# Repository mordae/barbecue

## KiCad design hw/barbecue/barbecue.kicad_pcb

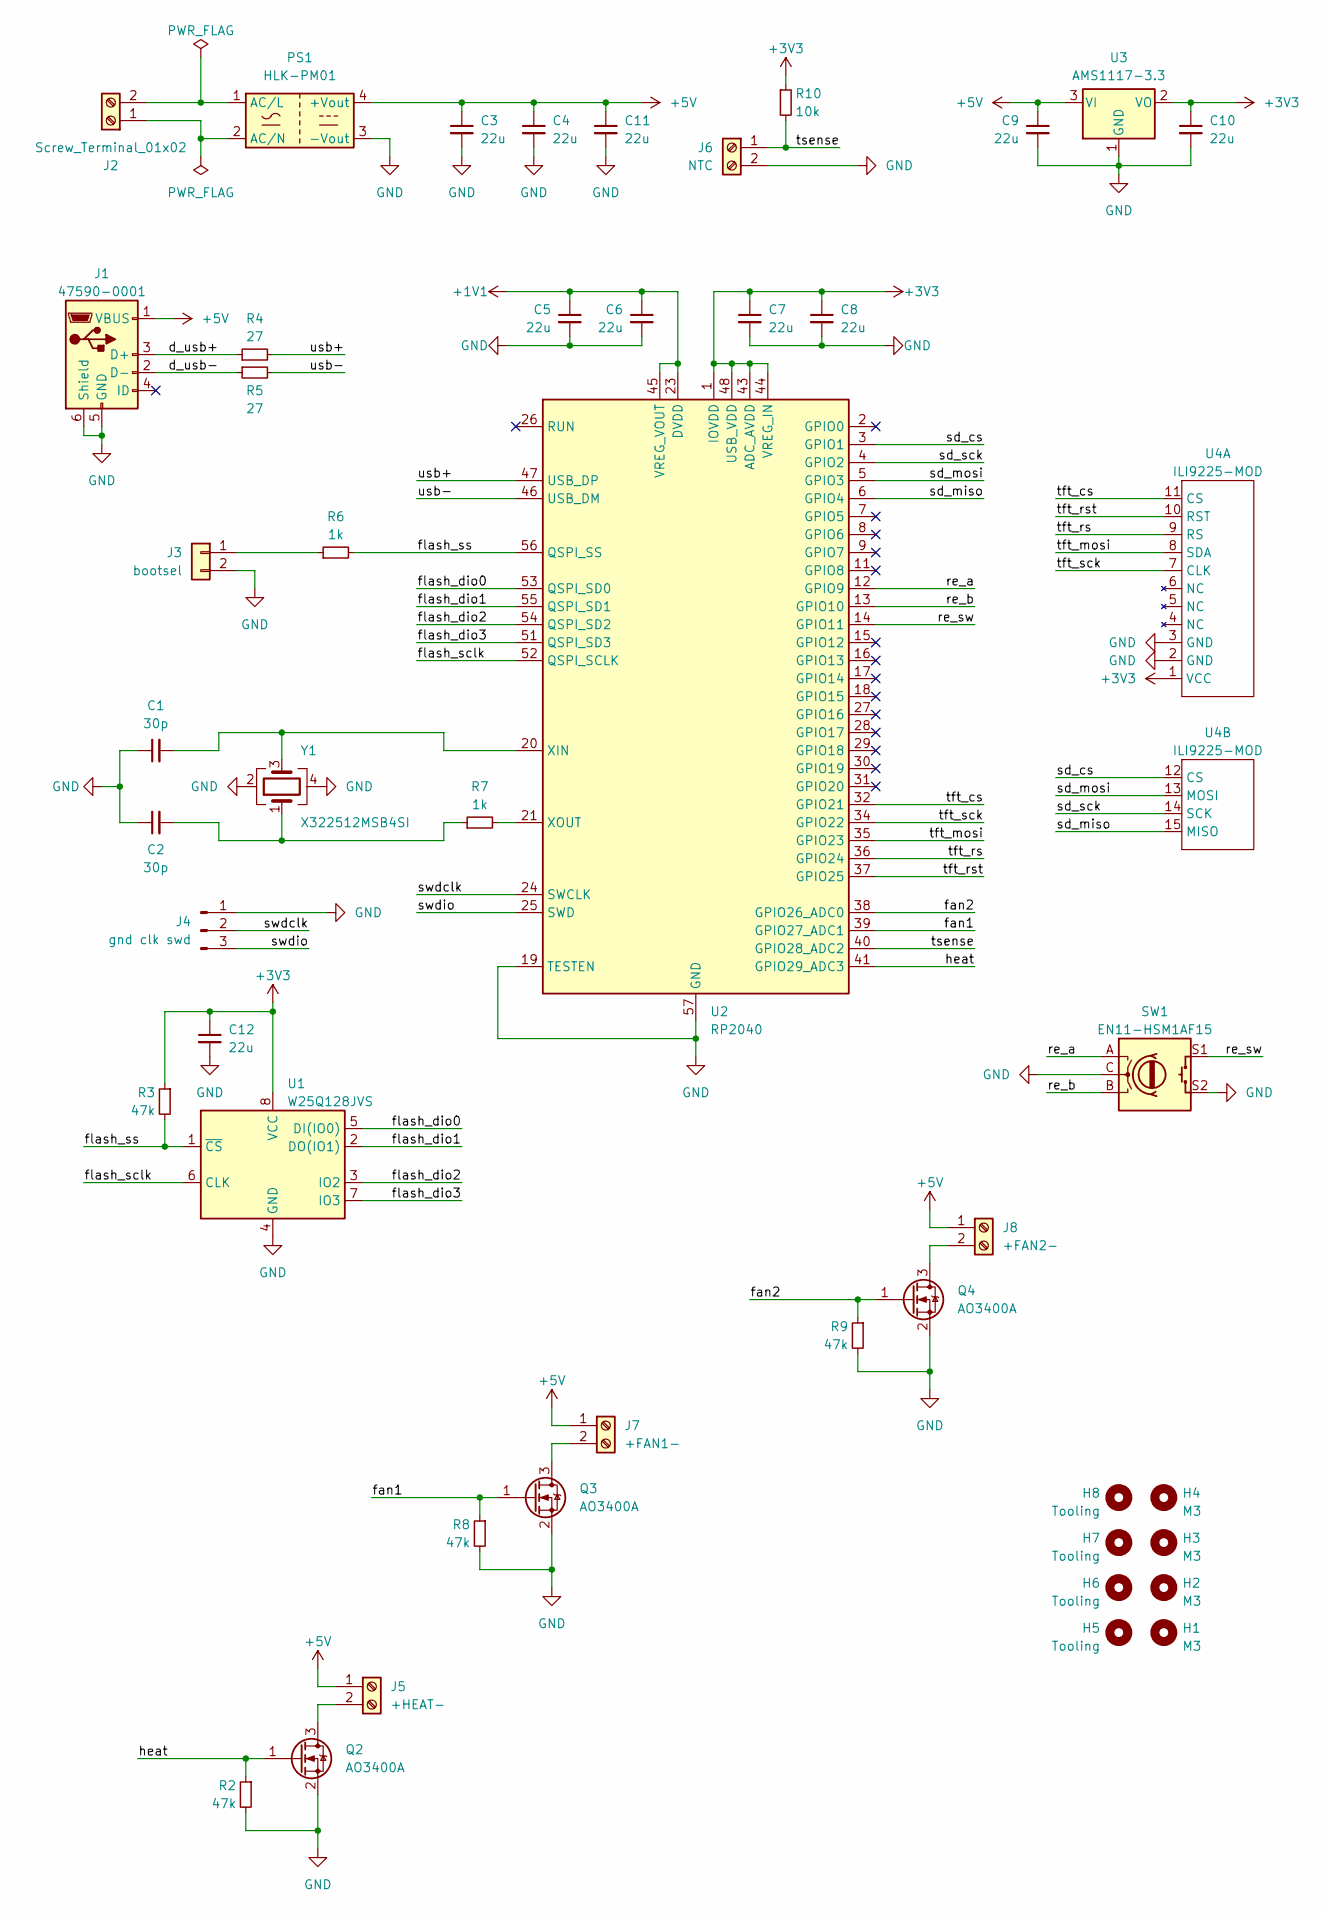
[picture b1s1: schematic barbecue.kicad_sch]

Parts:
C1, C2: 30p; C_0402_1005Metric
C3, C4, C5, C6, C7, C8, C9, C10, C11, C12: 22u; C_0603_1608Metric
H1, H2, H3, H4: M3; MountingHole_3.2mm_M3
H5, H6, H7, H8: Tooling; ToolingHole
J1: 47590-0001; USB_Micro-AB_Molex_47590-0001
J2: Screw_Terminal_01x02; TerminalBlock_Altech_AK300-2_P5.00mm
J3: bootsel; PinHeader_1x02_P2.54mm_Vertical
J4: gnd clk swd; PinHeader_1x03_P2.54mm_Vertical
J5: +HEAT-; TerminalBlock_TE_282834-2_1x02_P2.54mm_Horizontal
J6: NTC; TerminalBlock_TE_282834-2_1x02_P2.54mm_Horizontal
J7: +FAN1-; TerminalBlock_TE_282834-2_1x02_P2.54mm_Horizontal
J8: +FAN2-; TerminalBlock_TE_282834-2_1x02_P2.54mm_Horizontal
PS1: HLK-PM01; Converter_ACDC_HiLink_HLK-PMxx
Q2, Q3, Q4: AO3400A; SOT-23
R2, R3, R8, R9: 47k; R_0402_1005Metric
R4, R5: 27; R_0603_1608Metric
R6, R7: 1k; R_0402_1005Metric
R10: 10k; R_0603_1608Metric
SW1: EN11-HSM1AF15
U1: W25Q128JVS; SOIC-8_5.23x5.23mm_P1.27mm
U2: RP2040; QFN-56-1EP_7x7mm_P0.4mm_EP3.2x3.2mm
U3: AMS1117-3.3; SOT-223-3_TabPin2
U4: ILI9225-MOD
Y1: X322512MSB4SI; Crystal_SMD_3225-4Pin_3.2x2.5mm

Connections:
+1V1: C5.1, C6.1, U2.23 (DVDD), U2.45 (VREG_VOUT), U2.50 (DVDD)
+3V3: C7.1, C8.1, C10.1, C12.1, R3.1, R10.1, U1.8 (VCC), U2.1 (IOVDD), U2.10 (IOVDD), U2.22 (IOVDD), U2.33 (IOVDD), U2.42 (IOVDD), U2.43 (ADC_AVDD), U2.44 (VREG_IN), U2.48 (USB_VDD), U2.49 (IOVDD), U3.2 (VO), U4.1 (VCC)
+5V: C3.1, C4.1, C9.1, C11.1, J1.1 (VBUS), J5.1, J7.1, J8.1, PS1.4 (+Vout), U3.3 (VI)
/d_usb+: J1.3 (D+), R4.1
/d_usb-: J1.2 (D-), R5.1
/fan1: Q3.1 (G), R8.1, U2.39 (GPIO27_ADC1)
/fan2: Q4.1 (G), R9.1, U2.38 (GPIO26_ADC0)
/flash_dio0: U1.5 (DI(IO0)), U2.53 (QSPI_SD0)
/flash_dio1: U1.2 (DO(IO1)), U2.55 (QSPI_SD1)
/flash_dio2: U1.3 (IO2), U2.54 (QSPI_SD2)
/flash_dio3: U1.7 (IO3), U2.51 (QSPI_SD3)
/flash_sclk: U1.6 (CLK), U2.52 (QSPI_SCLK)
/flash_ss: R3.2, R6.2, U1.1 (~CS), U2.56 (QSPI_SS)
/heat: Q2.1 (G), R2.1, U2.41 (GPIO29_ADC3)
/re_a: SW1.A, U2.12 (GPIO9)
/re_b: SW1.B, U2.13 (GPIO10)
/re_sw: SW1.S1, U2.14 (GPIO11)
/sd_cs: U2.3 (GPIO1), U4.12 (CS)
/sd_miso: U2.6 (GPIO4), U4.15 (MISO)
/sd_mosi: U2.5 (GPIO3), U4.13 (MOSI)
/sd_sck: U2.4 (GPIO2), U4.14 (SCK)
/swdclk: J4.2, U2.24 (SWCLK)
/swdio: J4.3, U2.25 (SWD)
/tft_cs: U2.32 (GPIO21), U4.11 (CS)
/tft_mosi: U2.35 (GPIO23), U4.8 (SDA)
/tft_rs: U2.36 (GPIO24), U4.9 (RS)
/tft_rst: U2.37 (GPIO25), U4.10 (RST)
/tft_sck: U2.34 (GPIO22), U4.7 (CLK)
/tsense: J6.1, R10.2, U2.40 (GPIO28_ADC2)
/usb+: R4.2, U2.47 (USB_DP)
/usb-: R5.2, U2.46 (USB_DM)
GND: C1.1, C2.1, C3.2, C4.2, C5.2, C6.2, C7.2, C8.2, C9.2, C10.2, C11.2, C12.2, J1.5 (GND), J1.6 (Shield), J3.2, J4.1, J6.2, PS1.3 (-Vout), Q2.2 (S), Q3.2 (S), Q4.2 (S), R2.2, R8.2, R9.2, SW1.C, SW1.S2, U1.4 (GND), U2.19 (TESTEN), U2.57 (GND), U3.1 (GND), U4.2 (GND), U4.3 (GND), Y1.2, Y1.4
unnamed: C2.2, R7.1, Y1.1
unnamed: J2.1, PS1.2 (AC/N)
unnamed: J2.2, PS1.1 (AC/L)
unnamed: J3.1, R6.1
unnamed: J5.2, Q2.3 (D)
unnamed: J7.2, Q3.3 (D)
unnamed: J8.2, Q4.3 (D)
unnamed: C1.2, U2.20 (XIN), Y1.3
unnamed: R7.2, U2.21 (XOUT)

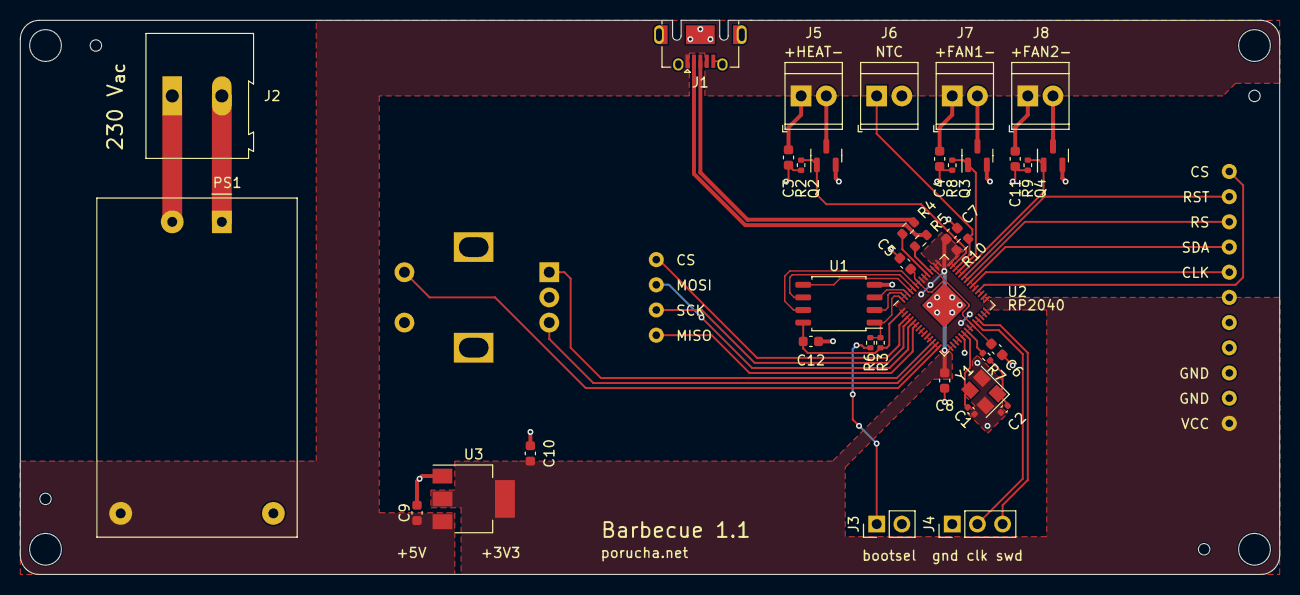
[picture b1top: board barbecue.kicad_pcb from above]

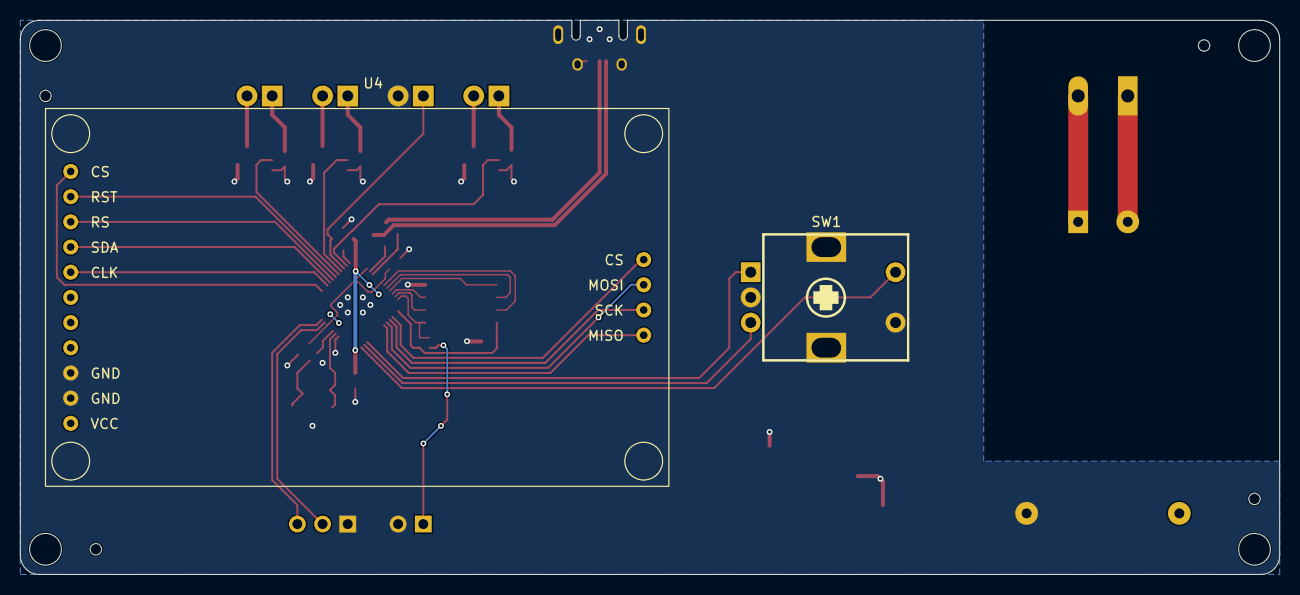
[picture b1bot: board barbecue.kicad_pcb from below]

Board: 2 copper layers, 127.0 x 55.9 mm, 47 parts (2 on the bottom side), 41 nets.

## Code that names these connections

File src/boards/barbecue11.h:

#pragma once

/* Delay to stabilize the oscillator. */
#if !defined(PICO_XOSC_STARTUP_DELAY_MULTIPLIER)
# define PICO_XOSC_STARTUP_DELAY_MULTIPLIER 64
#endif

/* QSPI flash access protocol selection. */
#define PICO_BOOT_STAGE2_CHOOSE_W25Q080 1
//#define PICO_BOOT_STAGE2_CHOOSE_GENERIC_03H 1

/* Flash access clock divider. */
#if !defined(PICO_FLASH_SPI_CLKDIV)
# define PICO_FLASH_SPI_CLKDIV 2
#endif

/* Total flash size in bytes. */
#if !defined(PICO_FLASH_SIZE_BYTES)
# define PICO_FLASH_SIZE_BYTES (16 * 1024 * 1024)
#endif

/* SD-Card */
#define SD_CS_PIN 1
#define SD_SCK_PIN 2
#define SD_MOSI_PIN 3
#define SD_MISO_PIN 4

/* Rotary encoder */
#define NUM_RENC 1
#define RENC_CW_PIN 9
#define RENC_CCW_PIN 10
#define RENC_SW_PIN 11
#define RENC_SENS 10

/* TFT Screen */
#define TFT_CS_PIN 21
#define TFT_SCK_PIN 22
#define TFT_MOSI_PIN 23
#define TFT_RS_PIN 24
#define TFT_RST_PIN 25

#define TFT_SWAP_XY 1
#define TFT_FLIP_X 0
#define TFT_FLIP_Y 0
#define TFT_SPI_DEV spi0

/* Other TFT parameters. */
#if !defined(TFT_BAUDRATE)
# define TFT_BAUDRATE (64 * 1000 * 1000)
#endif

/* Fan and heater control */
#define FAN1_PIN 27
#define FAN2_PIN 26
#define HEAT_PIN 29

/* NTC thermistor */
#define TSENSE_PIN 28

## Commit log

2022-12-15 Initial import
2022-12-26 Small board fixes
2022-12-26 Demo app
2022-12-26 Save board-related options in the CMakeLists.txt
2022-12-26 Enable stdio over USB
2022-12-27 Move code to the src/ subdir
2022-12-27 Test temperature readout
2022-12-29 Decent thermometer demo
2022-12-30 Use lower flash clock divider
2022-12-30 Increase display access speed
2022-12-30 Fix board PWM outputs
2023-01-01 Assorted small improvements
2023-01-05 Add a simple task scheduler
2023-01-05 task: Use narrower includes
2023-01-05 task: implement yield_to_all
2023-01-06 task: fix and introduce SDK compat layer
2023-01-06 renc: interrupt-based rotary encoder input
2023-01-06 task: hook tasks into the SDK
2023-01-06 renc: remove leftover esp32 code
2023-01-06 task: improve the interface a little bit
2023-01-06 ili9225: make sure to avoid division
2023-01-07 Use builtin integer divider
2023-01-07 task: add task_run_loop
2023-01-07 Use tasks for the main application
2023-01-07 Use a more hacky way too hook in task compat
2023-01-07 renc: handle sensitivity properly
2023-01-07 renc: remove leftover commented-out printf
2023-01-07 Remove font binary file, we have .c
2023-01-07 renc: annotate isr properly and other cleanups
2023-01-07 Add task statistics tracking
2023-01-07 task: adjust stats format
2023-01-07 task: add task_create_on_core
2023-01-07 Run screen task on the second core
2023-01-07 Fix task stats header format
2023-01-07 task: move stats functions above the hooks
2023-01-07 task: replace task_yield_to_any with task_yield_until_event
2023-01-07 More per-core cleanup
2023-01-07 task: protect creation and destruction with a lock
2023-01-07 task: report on task statuses
2023-01-07 task: use memory barriers when unblocking tasks
2023-01-07 task: redesign blocking to avoid needless wakeups
2023-01-07 ili9225: separate tft_swap_buffers for parallelism
2023-01-08 task: redesign readiness and stack handling
2023-01-08 Improve calibration
2023-01-08 Wait up to 1s for console
2023-01-09 Increase input_task stack size
2023-01-09 Increase stats task priority
    This avoids starvation by more greedy tsense task.
2023-01-09 ili9225: Parallelize transmission using DMA
2023-01-09 task: avoid deadlock with short alarm timeout
2023-01-09 Limit screen to 30 fps
2023-01-09 Use more integer math in tsense
2023-01-09 Smooth less
2023-01-09 task: init the default alarm pool
2023-01-10 renc: redesign for improved reliability
2023-01-10 renc: handle maximum rotation speed correctly
2023-01-13 Calibrate higher temps against my multimeter
2023-01-16 Version 1.1 as sent to manufacturing
2023-02-06 Fixes and new board
2023-02-07 Add ST7735 display and implement basic thermostat
2023-02-07 Generalize TFT drivers and use common <tft.h>
2023-02-07 Allow display selection via cmake -DDISPLAY=...
2023-02-07 Extract display driver
2023-02-08 Turn off fans once cooled to the ambient level
